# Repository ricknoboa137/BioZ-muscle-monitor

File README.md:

# BioZ Muscle Monitor — Reverse-Engineered Hardware

A portable, battery-powered bioimpedance spectroscopy (BIS) device that measures
biceps muscle impedance during and after exercise, to track fatigue and fluid
shift. Tetrapolar (4-electrode) measurement, 20 frequencies swept once per
second, 2 hours of on-device logging, BLE offload, ~21 days between charges.

This project reverse-engineers the device described in an unpublished 2026
undergraduate thesis from a Hungarian technical university's electrical
engineering programme (cited without naming the student, supervisors, or
institution, out of respect for their privacy — see
[`00-context-reverse-engineered.md`](00-context-reverse-engineered.md) for the
full extracted specification). It is a *corrected* reproduction, not a
transcription: every part number is verified against its real datasheet, and
every defect found in the source design — swapped connections, missing
decoupling, wrong ground references — is called out and fixed rather than
copied forward.

Built as a working test of an automated hardware-design pipeline: schematic →
PCB layout → 3D-printable enclosure, each stage driven by an agent that reads
real datasheets, verifies its own work against real design-rule checks and the
manufacturer's own documentation, and refuses to silently relax a constraint or
claim something is finished when it isn't.

## Status — read this before trusting any file in here as final

**Schematic: done.** Verified against manufacturer datasheets, 8 defects found
in the source design fixed and documented, KiCad-ready net list.

**PCB layout: in progress, not fab-ready.** The board routes and passes DRC
against its real custom design rules (fixed this session — see below), but
still has open items: unconnected nets remaining, and several trace-width
categories still need widening/re-routing. See
[`pcb/CHECKPOINT.md`](pcb/CHECKPOINT.md) for the exact, currently-accurate
state — it is updated continuously and is more current than this README.

**Enclosure: in progress.** A parametric two-part case exists in SOLIDWORKS
with STL exports, built to fit the current (grown) board size and a
side-by-side battery arrangement. Several dimensions (behind-panel depth for
the pushbutton, cutouts for the slide switch and magnetic connector) are still
provisional pending parts that could not be fully verified from public
datasheets. See [`case/CHECKPOINT.md`](case/CHECKPOINT.md).

### A finding worth knowing about before you trust a "0 errors" claim anywhere in this history

For a significant part of this project, the PCB's custom design rules
(patient-electrode clearance, RF isolation, the ground-plane split integrity)
were **silently inactive** — one malformed rule voided the entire rules file,
and even fixed, rule ordering meant permissive defaults would have overridden
the strict ones. Every earlier "0 DRC errors" claim in this project's history
was checked against KiCad's generic defaults, not the actual project rules.
This has since been found, fixed, and verified with a controlled test (a
deliberately-bad track that must trigger a specific named rule) rather than
just re-running DRC and hoping. The real violations that were hiding behind it
— including patient-safety clearance and ground-split violations — are being
worked through; see the PCB checkpoint for the current count. This is
disclosed here deliberately: a device that will contact human skin should not
have its safety-relevant checks trusted just because a tool once reported zero.

## Layout

```
00-context-reverse-engineered.md   Extracted, datasheet-verified spec from the source thesis
pcb-brief.md                       Schematic -> PCB handoff: constraints, net classes, keepouts
schematic.html                     Schematic drawing source
docx-source.txt                    Design dossier source (OOXML builder markup)
BioZ-Muscle-Monitor-Design-Dossier-RevB.docx   Full schematic-stage design dossier
BioZ-Muscle-Monitor-Layout-RevB.docx           PCB layout dossier
img/                               Schematic sheet renders

pcb/
  BioZ-Muscle-Monitor.kicad_*      KiCad 10 project, board, net classes, custom DRC rules
  BioZ-Muscle-Monitor.pretty/      Custom footprints (0.4mm-pitch WLP, antenna, shield frame, etc.)
  CHECKPOINT.md                    Authoritative, continuously-updated layout status
  placement-plan.md, routing-order.md, pre-gerber-checklist.md
  scripts/                         Reproducible pcbnew/KiCad automation used to build and verify the board
  img-layout/, img-3d/             Rendered plots and 3D views

case/
  CHECKPOINT.md                    Authoritative, continuously-updated enclosure status
  cad/                             SOLIDWORKS parts + the Python build scripts that generate them
  stl/                             Print-ready STL exports
```

## Tooling

KiCad 10.0.5, Freerouting 2.3.0 (Java 25 JRE), SOLIDWORKS 2026 SP03 via its COM
API, and a dependency-free OOXML `.docx` builder — no Python required for the
schematic or PCB documentation stages. See each `CHECKPOINT.md` for the
specific hard-won API/tooling traps found and fixed along the way.

## What this is not

Not a certified medical device. Not reviewed against IEC 60601-1 patient
auxiliary current limits (an open item, flagged as blocking any human use in
the design dossier). Not fabricated or assembled — this is a verified design,
not a built and tested unit.

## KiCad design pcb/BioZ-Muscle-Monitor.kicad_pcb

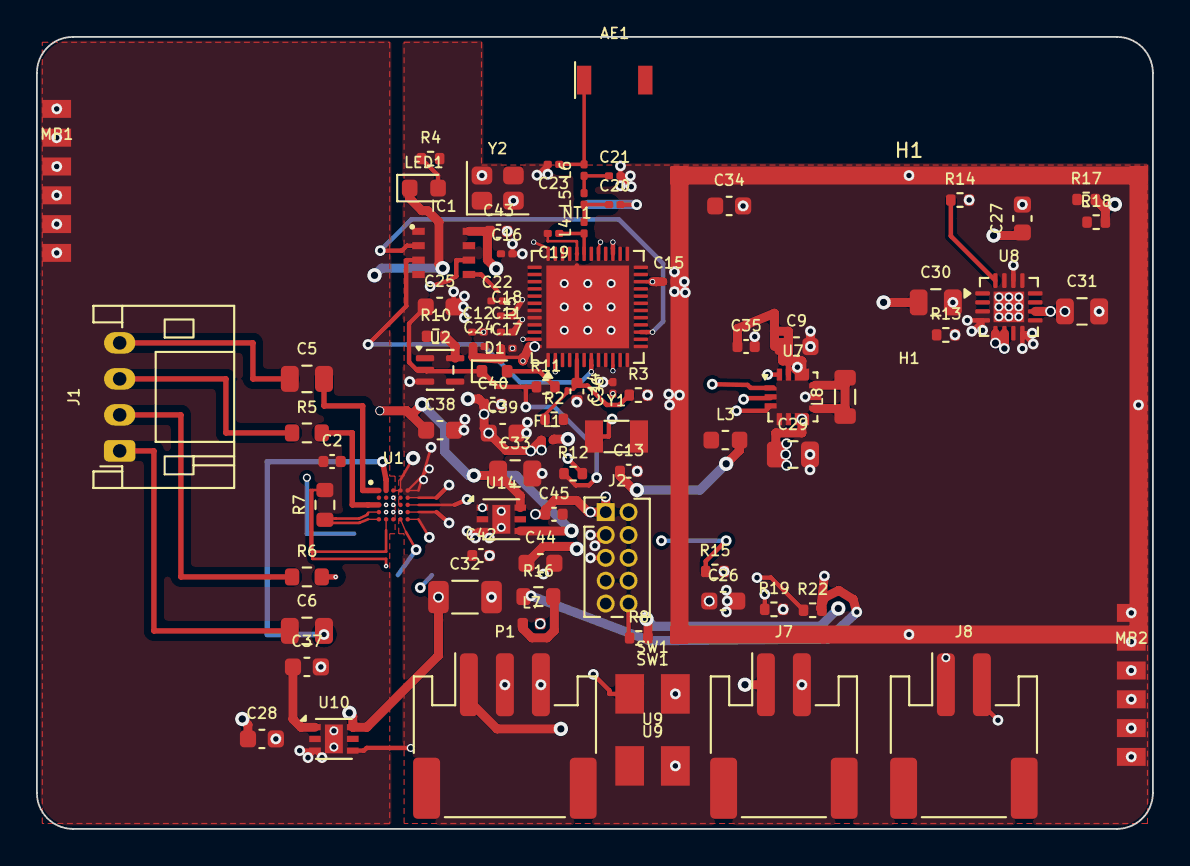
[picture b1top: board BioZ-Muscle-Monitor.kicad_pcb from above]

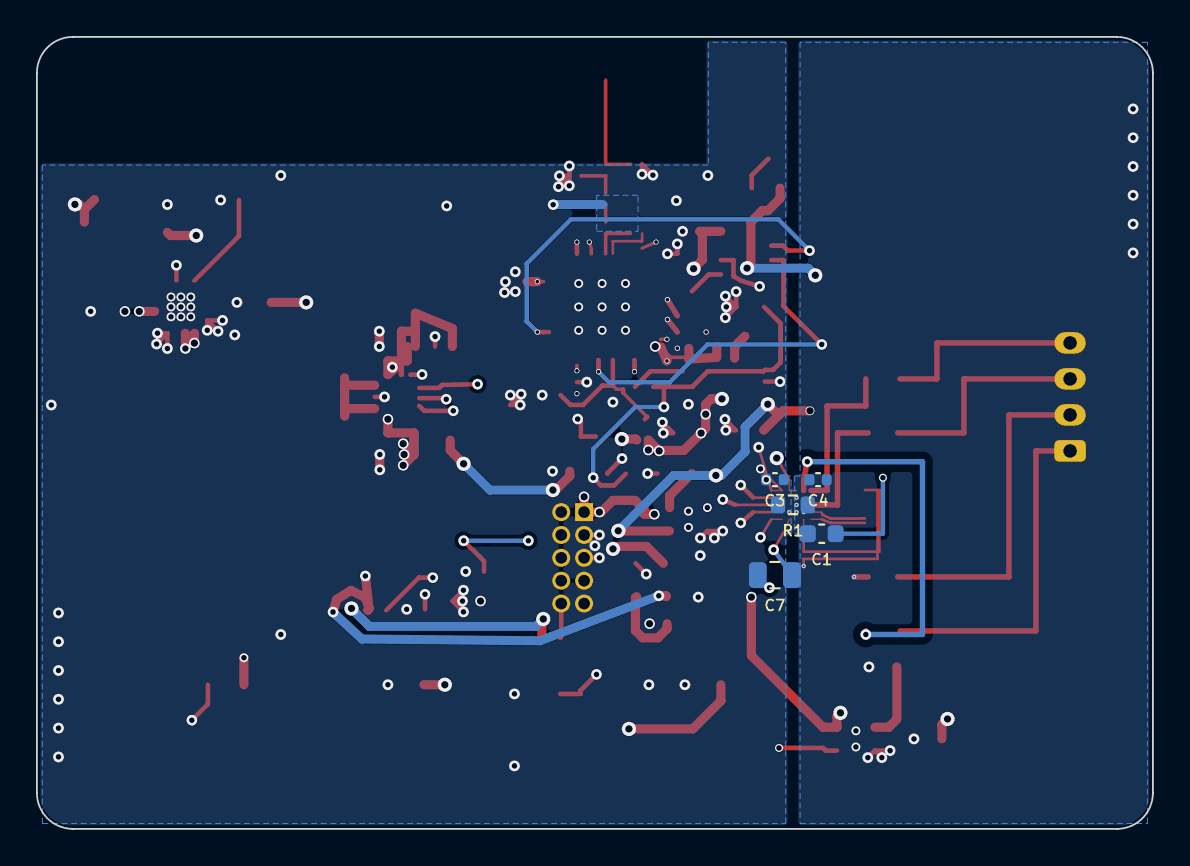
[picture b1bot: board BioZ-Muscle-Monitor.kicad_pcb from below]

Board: 6 copper layers, 62.0 x 44.0 mm, 92 parts (5 on the bottom side), 66 nets.

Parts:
AE1: WE-MCA 74889302450; Wurth_WE-MCA_74889302450
C1: 1u X5R VREF; C_0603_1608Metric
C2, C13, C40, C42: 10u; C_0402_1005Metric
C3: 100n DVDD; C_0402_1005Metric
C4: 100n AVDD; C_0402_1005Metric
C5, C6, C7: 47n; C_0805_2012Metric
C9: 22u; C_0603_1608Metric
C11, C12: 2u2; C_0201_0603Metric
C14, C15, C16, C17, C24: 100n; C_0201_0603Metric
C18: 10n DECD; C_0201_0603Metric
C19: 1p5; C_0201_0603Metric
C20: 2p0; C_0201_0603Metric
C21: 0p3; C_0201_0603Metric
C22: 10n DECA/DECRF; C_0201_0603Metric
C23: 3p9; C_0201_0603Metric
C25: 10n; C_0603_1608Metric
C26, C27, C28, C37, C38, C39, C44: 1u; C_0603_1608Metric
C29, C33: 10u; C_0805_2012Metric
C30, C31: 4u7; C_0805_2012Metric
C32: 3u3; C_1206_3216Metric
C34: 1u BIAS; C_0603_1608Metric
C35, C36, C43, C45: 100n; C_0402_1005Metric
D1: BAT54-02V; D_SOD-523
FL1: 120R; L_0201_0603Metric
H1: WE-SHC 36103255; Wurth_WE-SHC_36103255_26x26mm
IC1: CY15V108QI; Infineon_GQFN-8_3.23x3.28mm
J1: S4B-PH-K-S; JST_PH_S4B-PH-K_1x04_P2.00mm_Horizontal
J2: 62201021121 SWD; PinHeader_2x05_P1.27mm_Vertical
J7: S2B-PH-SM4-TB BATT; JST_PH_S2B-PH-SM4-TB_1x02-1MP_P2.00mm_Horizontal
J8: S2B-PH-SM4-TB SW; JST_PH_S2B-PH-SM4-TB_1x02-1MP_P2.00mm_Horizontal
L3: 4u7; L_0603_1608Metric
L4: 2n7; L_0201_0603Metric
L5, L6: 3n5; L_0201_0603Metric
L7: 32n; L_0402_1005Metric
L8: 1u0; L_0805_2012Metric
LED1: APT1608SURCK; LED_0603_1608Metric
MP1: edge pads L; EdgePads_1x6_P1.6mm
MP2: edge pads R; EdgePads_1x6_P1.6mm
NT1: VSS_PA-GNDD; NetTie-2_0.25mm_P0.65mm
P1: S3B-PH-SM4-TB; JST_PH_S3B-PH-SM4-TB_1x03-1MP_P2.00mm_Horizontal
R1: 0R STITCH; R_0603_1608Metric
R2: 1M; R_0402_1005Metric
R3, R22: 100k; R_0402_1005Metric
R4: 200R; R_0402_1005Metric
R5, R6: 40k2; R_0603_1608Metric
R7: 680R 0.1%; R_0603_1608Metric
R8: 1k; R_0402_1005Metric
R10: 2k2; R_0402_1005Metric
R11: 220k; R_0402_1005Metric
R12: 1k6; R_0402_1005Metric
R13: 2k55 ILIM; R_0402_1005Metric
R14: 2k21 ISET; R_0402_1005Metric
R15: 634k 1%; R_0402_1005Metric
R16: 0R1; R_0603_1608Metric
R17, R18: 1k5; R_0402_1005Metric
R19: 10k; R_0402_1005Metric
SW1: 52-03-80 (panel); WirePads_1x2_P2.54mm
U1: MAX30009ENA+; MAX30009ENA_WLP25_2.03x2.03_P0.4mm
U2: SN74LVC1G14; SOT-353_SC-70-5
U5: nRF54L15-QFAA; QFN-48-1EP_6x6mm_P0.4mm_EP4.6x4.6mm
U7: MAX77827BEFD+T; Maxim_FC2QFN-14_2.5x2.5mm_P0.5mm
U8: BQ24073RGT; QFN-16-1EP_3x3mm_P0.5mm_EP1.7x1.7mm
U9: 103AT-2 (on cell); WirePads_1x2_P2.54mm
U10: ADPL40502-1.8 A; DFN-6-1EP_2x2mm_P0.65mm_EP1x1.6mm
U14: ADPL40502-1.8 D; DFN-6-1EP_2x2mm_P0.65mm_EP1x1.6mm
Y1: 32.768kHz ABS06; Crystal_SMD_3215-2Pin_3.2x1.5mm
Y2: 32MHz ABM10; Crystal_SMD_2520-4Pin_2.5x2.0mm

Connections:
AFE_CS: U1.D2, U5.16
AFE_INT: U1.E5, U5.27
AFE_PWR_EN: U5.29, U10.4
ANT: C19.1, L4.1, U5.31
BIAS: C34.1, U7.5
BTN_N: U2.4, U5.24
BTN_PU: D1.2, R10.1, R11.2
BTN_RC: C25.1, D1.1, R11.1, R12.1, U2.2
BTN_SW: R12.2, SW1.1
CAL_F: R7.1, U1.A4, U1.A5
CAL_S: R7.2, U1.B4, U1.B5
DCC: C11.1, C12.1, L3.1, U5.46
DECA_RF: C22.1, U5.33, U5.43
DECD: C18.1, U5.45
DRVSJ: C7.2, U1.C4
DRVXC: C7.1, U1.D5
EL_DRVN: C6.2, U1.B1
EL_DRVP: C5.2, U1.A1
EL_SENN: R6.2, U1.B3
EL_SENP: R5.2, U1.A3
FPWM_CTL: R19.1, U5.28, U7.14
GNDA: C1.2, C2.2, C4.2, C28.2, C37.2, MP1.1, MP1.2, MP1.3, MP1.4, MP1.5, MP1.6, R1.1, U1.C3, U10.3, U10.7
GNDD: C3.2, C9.2, C11.2, C12.2, C13.2, C14.2, C15.2, C16.2, C17.2, C18.2, C21.2, C22.2, C23.2, C24.2, C25.2, C26.2, C27.2, C29.2, C30.2, C31.2, C32.2, C33.2, C34.2, C35.2, C36.2, C38.2, C39.2, C40.2, C42.2, C43.2, C44.2, C45.2, H1.1, IC1.4, J2.3, J2.5, J2.9, J7.2, MP2.1, MP2.2, MP2.3, MP2.4, MP2.5, MP2.6, NT1.2, P1.2, P1.3, R1.2, R3.2, R13.2, R14.2, R15.2, R19.2, SW1.2, U1.D4, U1.E1, U2.3, U5.44, U5.49, U7.4, U7.9, U8.4, U8.8, U8.14, U8.15, U8.17, U9.2, U14.3, U14.7, Y2.2, Y2.4
ILIM: R13.1, U8.12
ISET: R14.1, U8.16
LED_K: R4.2, U5.23
LED_K_R: LED1.2, R4.1
LX: L8.1, L8.2, U7.8, U7.10
MEM_CS: IC1.1, U5.14
MEM_WP: IC1.3, U5.7
POK: R22.1, U7.2
PT_E1: C5.1, J1.4
PT_E2: J1.2, R6.1
PT_E3: J1.3, R5.1
PT_E4: C6.1, J1.1
RF_A: C20.1, L4.2, L5.1
RF_ANT: AE1.1, C23.1, L6.2
RF_B: C21.1, L5.2, L6.1
SEL: R15.1, U7.1
SPI_SCK: IC1.6, U1.E4, U5.12
SPI_SDI: IC1.2, U1.E2, U5.15
SPI_SDO: IC1.5, U1.E3, U5.13
SWDCLK: J2.4, U5.26
SWDIO: J2.2, U5.25
SWO: J2.6, U5.18
SW_EN: J8.2, U7.3
TS_NTC: U8.1, U9.1
V1P8A: C2.1, C3.1, C4.1, C37.1, C42.1, U1.C1, U1.D1, U10.1
V1P8D: C39.1, C40.1, C43.1, C44.1, C45.1, FL1.1, IC1.8, J2.1, R8.2, R10.2, R17.2, R18.2, U2.5, U14.1
V2P5: C9.1, C35.1, R16.1, R22.2, U7.11, U7.13
V2P5F: C28.1, C32.1, C33.1, C38.1, L7.2, LED1.1, U10.6, U14.4, U14.6
V2P5FA: L7.1, R16.2
VBAT_SENSE: C36.1, R2.1, R3.1, U5.5
VDD_nRF: C13.1, C14.1, C15.1, C16.1, C17.1, C24.1, FL1.2, L3.2, U5.10, U5.22, U5.36, U5.47, U5.48
VIN_EXT: C27.1, P1.1, U8.13
VREF: C1.1, U1.C2
VSS_PA: C19.2, NT1.1, U5.32
V_BAT: C30.1, J7.1, U8.2, U8.3
V_SYS: C26.1, C29.1, C31.1, J8.1, R2.2, U7.6, U8.5, U8.6, U8.10, U8.11
XC1: U5.34, Y2.1
XC2: U5.35, Y2.3
XL1: U5.1, Y1.1
XL2: U5.2, Y1.2
nCHG: R18.1, U5.8, U8.9
nPGOOD: R17.1, U5.6, U8.7
nRESET: J2.10, R8.1, U5.30

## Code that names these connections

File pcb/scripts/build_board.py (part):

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add("C5", "47n", *C0805, 15.0, 19.0, 0, "T", {"2": "EL_DRVP", "1": "PT_E1"})
add("C6", "47n", *C0805, 15.0, 33.0, 0, "T", {"2": "EL_DRVN", "1": "PT_E4"})

add("C2", "10u", *C0402, 16.4, 23.0, 0, "T", {"1": "V1P8A", "2": GA}, pin=False)
add("C37", "1u", *C0603, 15.0, 35.0, 0, "T", {"1": "V1P8A", "2": GA}, pin=False)
add("C42", "10u", *C0402, 22.6, 22.6, 0, "T", {"1": "V1P8A", "2": GD}, pin=False)
add("U10", "ADPL40502-1.8 A", "Package_DFN_QFN",
    "DFN-6-1EP_2x2mm_P0.65mm_EP1x1.6mm", 16.5, 39.0, 0, "T",
    {"1": "V1P8A", "2": "", "3": GA, "4": "AFE_PWR_EN", "5": "", "6": "V2P5F",
     "7": GA})
add("C28", "1u", *C0603, 12.5, 39.0, 0, "T", {"1": "V2P5F", "2": GA}, pin=False)
# Electrode harness, left (44 mm) edge -- opposite short edge from P1.
add("J1", "S4B-PH-K-S", "Connector_JST",
    "JST_PH_S4B-PH-K_1x04_P2.00mm_Horizontal", 4.6, 23.0, 90, "T",
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    pin=False); attach("C22", "U5", "43", 0.10, dirn="W")
add("C18", "10n DECD", *C0201, 0, 0, 0, "T", {"1": "DECD", "2": GD},
    pin=False); attach("C18", "U5", "45", 0.10, dirn="W")
add("C11", "2u2", *C0201, 0, 0, 0, "T", {"1": "DCC", "2": GD}, pin=False)
attach("C11", "U5", "46", 0.10, dirn="W")
add("C12", "2u2", *C0201, 0, 0, 0, "T", {"1": "DCC", "2": GD}, pin=False)
attach("C12", "U5", "46", 1.20, dirn="W")
add("C36", "100n", *C0402, 0, 0, 0, "T", {"1": "VBAT_SENSE", "2": GD},
    pin=False); # rot 270 so C36 pad 1 (VBAT_SENSE) faces the pin and pad 2 (GNDD) points
# away: otherwise the ground pad sits between the pin and the signal pad.
attach("C36", "U5", "5", 0.10, rot=270, dirn="S")     # brief 4.6: at the MCU pin
add("L3", "4u7", *L0603, 30.0, 22.4, 0, "T", {"1": "DCC", "2": "VDD_nRF"})
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add("IC1", "CY15V108QI", LOCAL, "Infineon_GQFN-8_3.23x3.28mm",
    22.6, 12.0, 0, "T", {"1": "MEM_CS", "2": "SPI_SDI", "3": "MEM_WP", "4": GD,
                         "5": "SPI_SDO", "6": "SPI_SCK", "7": "", "8": "V1P8D"})
add("C43", "100n", *C0402, 0, 0, 0, "T", {"1": "V1P8D", "2": GD}, pin=False)
attach("C43", "IC1", "8", 0.10)                    # brief 5 priority 8

add("U14", "ADPL40502-1.8 D", "Package_DFN_QFN",
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    {"1": "LX", "2": "LX"})
add("C29", "10u", *C0805, 42.0, 23.2, 0, "T", {"1": "V_SYS", "2": GD})
add("C9", "22u", *C0603, 42.2, 17.2, 0, "T", {"1": "V2P5", "2": GD})
add("C26", "1u", *C0603, 39.0, 23.2, 0, "T", {"1": "V_SYS", "2": GD}, pin=False)
add("C35", "100n", *C0402, 39.4, 17.2, 0, "T", {"1": "V2P5", "2": GD})
add("C34", "1u BIAS", *C0603, 38.4, 20.0, 0, "T", {"1": "BIAS", "2": GD},
    pin=False)
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    "6": "V_SYS", "7": "nPGOOD", "8": GD, "9": "nCHG", "10": "V_SYS",
    "11": "V_SYS", "12": "ILIM", "13": "VIN_EXT", "14": GD, "15": GD,
    "16": "ISET", "17": GD})
add("C30", "4u7", *C0805, 0, 0, 0, "T", {"1": "V_BAT", "2": GD}, pin=False)
attach("C30", "U8", "2", 0.10, dirn="W")                      # brief 5 priority 9
add("C31", "4u7", *C0805, 0, 0, 0, "T", {"1": "V_SYS", "2": GD}, pin=False)
attach("C31", "U8", "10", 0.10, dirn="E")
add("C27", "1u", *C0603, 0, 0, 0, "T", {"1": "VIN_EXT", "2": GD}, pin=False)
attach("C27", "U8", "13", 1.7, dirn="N")
add("R13", "2k55 ILIM", *R0402, 50.4, 19.0, 0, "T", {"1": "ILIM", "2": GD},
    pin=False)
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add("R10", "2k2", *R0402, 24.4, 16.6, 0, "T", {"1": "BTN_PU", "2": "V1P8D"},
    pin=False)
add("D1", "BAT54-02V", "Diode_SMD", "D_SOD-523", 24.4, 18.4, 0, "T",
    {"1": "BTN_RC", "2": "BTN_PU"}, pin=False)
add("R12", "1k6", *R0402, 22.6, 18.8, 0, "T", {"1": "BTN_RC", "2": "BTN_SW"},
    pin=False)
add("R8", "1k", *R0402, 30.4, 36.0, 0, "T", {"1": "nRESET", "2": "V1P8D"},
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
